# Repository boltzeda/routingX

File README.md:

# routingX

**routingX** is an automated PCB routing tool designed to route already placed KiCad PCB layouts. It takes a placed PCB as input, identifies unrouted connections, and attempts to complete the routing while respecting the board's design constraints.

The router generates a routed KiCad PCB file along with routing reports that help users inspect the routing results and identify any remaining unrouted connections.

## Features

- **Automated PCB Routing:** Routes unrouted connections in an already placed KiCad PCB.
- **Design Rule Awareness:** Supports routing-rule configuration through an optional DRC JSON file.
- **Configurable Via Cost:** Allows users to control the cost associated with via insertion.
- **Partial Routing Support:** Generates a partially routed PCB when all connections cannot be completed.
- **Routing Reports:** Produces JSON reports containing routing results and route details.
- **KiCad Compatibility:** Uses KiCad's PCB tools and Python bindings for board processing.

## Prerequisites

### 1. KiCad 10

Install KiCad 10 with the PCB Editor's `pcbnew` Python binding and `kicad-cli`.

Download KiCad from the [official KiCad download page](https://www.kicad.org/download/).

Linux users can refer to the [distribution-specific installation instructions](https://www.kicad.org/download/linux-distros/).

Verify the installation:

```bash
kicad-cli version
```

Ensure that the `pcbnew` Python module is accessible from the Python environment used to run the router.

### 2. Python

Python **3.13 or later** is required.

Verify your Python version:

```bash
python --version
```

### 3. Python Dependencies

Install the required Python packages from `requirements.txt`.

```bash
python -m pip install -r routingX/requirements.txt
```

## Installation

Clone the repository:

```bash
git clone <repository-url>
```

Navigate to the repository directory:

```bash
cd <repository-name>
```

Install the dependencies:

```bash
python -m pip install -r routingX/requirements.txt
```

Make sure KiCad 10 and its Python bindings are properly configured before running the router.

## Usage

The router accepts an already placed KiCad PCB file (`.kicad_pcb`) as input.

Run the following command from the directory containing the `routingX/` package folder:

```bash
python -m routingX path/to/placed_board.kicad_pcb
```

By default, the router generates the following output:

- **Complete routing:** `<board>_routed.kicad_pcb`
- **Partial routing:** `<board>_partial.kicad_pcb`

The output files are generated in the same directory as the input board.

### Custom Output Path

To specify a custom output location:

```bash
python -m routingX path/to/placed_board.kicad_pcb \
    --out path/to/routed_board.kicad_pcb
```

### Command-Line Options

| Argument | Description | Default |
|---|---|---|
| Input PCB | Path to the placed KiCad PCB file | Required |
| `--out <path>` | Specifies the output PCB file path | Automatically generated |
| `--drc <path.json>` | Provides custom routing-rule values | Built-in defaults |
| `--via-cost <value>` | Controls the cost associated with via insertion | `2.0` |
| `--quiet` | Reduces progress and informational output | Disabled |

### Example with Custom Parameters

```bash
python -m routingX boards/example.kicad_pcb \
    --out output/example_routed.kicad_pcb \
    --via-cost 2.0 \
    --quiet
```

To provide custom routing rules:

```bash
python -m routingX boards/example.kicad_pcb \
    --drc config/drc_rules.json \
    --out output/example_routed.kicad_pcb
```

If no DRC configuration is provided, the router uses its built-in defaults and raises them to satisfy the board's minimum constraints.

## Output Files

The router generates the following files depending on the routing result:

| Output | Description |
|---|---|
| `*_routed.kicad_pcb` | KiCad PCB file generated when routing is complete. |
| `*_partial.kicad_pcb` | Partially routed PCB file generated when some connections remain unrouted. |
| Routing result JSON | Summary of the routing execution and its result. |
| `<output-path>.routes.json` | Detailed routing information for inspection and analysis. |

The partial PCB output allows users to open the board in KiCad and inspect completed and remaining connections.

## Design Rule Verification

After routing, always perform a Design Rule Check (DRC) using KiCad's native DRC functionality.

A successful routing result indicates that the router completed its routing task. However, it does not guarantee that the board is free from all electrical, physical, or manufacturing-related violations.

Recommended verification:

1. Open the generated PCB file in KiCad PCB Editor.
2. Run the native Design Rule Checker (DRC).
3. Inspect unrouted connections, clearance violations, and other reported issues.
4. Review the board before proceeding to manufacturing.

## License

This project is licensed under the **MIT License**.

See the [LICENSE](LICENSE) file for more information.

## Acknowledgements

routingX is part of the BoltzPCB ecosystem, focused on automating and improving PCB design workflows.

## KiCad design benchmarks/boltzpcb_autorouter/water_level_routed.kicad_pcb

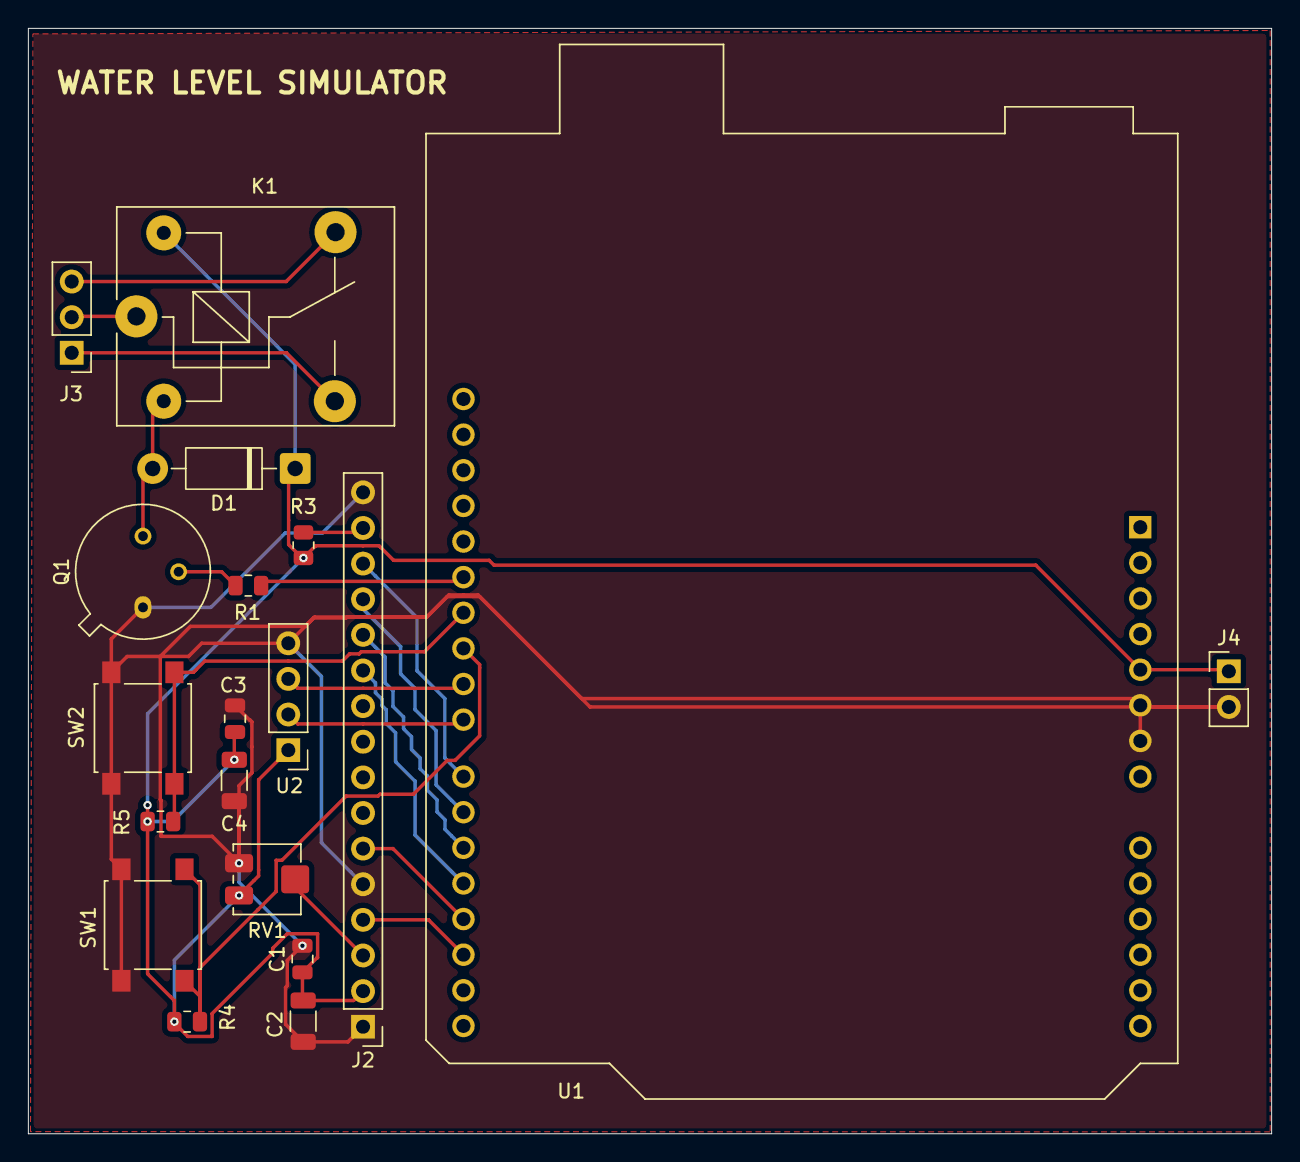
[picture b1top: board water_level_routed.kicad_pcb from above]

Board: 2 copper layers, 88.6 x 78.8 mm, 19 parts (0 on the bottom side), 20 nets.

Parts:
C1, C3: 100nF; C_0805_2012Metric
C2, C4: 10uF; C_1206_3216Metric
D1: 1N4007; D_DO-41_SOD81_P10.16mm_Horizontal
J2: Conn_01x16_Pin; PinHeader_1x16_P2.54mm_Vertical
J3: RELAY_OUT; PinHeader_1x03_P2.54mm_Vertical
J4: POWER_IN; PinHeader_1x02_P2.54mm_Vertical
K1: SANYOU_SRD_Form_C; Relay_SPDT_SANYOU_SRD_Series_Form_C
Q1: 2N2219; TO-39-3
R1: 1k; R_0805_2012Metric
R3: 220R; R_0805_2012Metric
R4, R5: 10k; R_0805_2012Metric
RV1: 10k; Potentiometer_Bourns_3224J_Horizontal
SW1: SET; SW_SPST_B3S-1000
SW2: AUTO/MANUAL; SW_SPST_B3S-1000
U1: Arduino_UNO_R3
U2: HC-SR04; PinHeader_1x04_P2.54mm_Vertical

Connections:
+5V: C1.1, C2.1, C3.1, C4.1, D1.1 (K), J2.2, J4.1, K1.5, R3.2, R4.1, R5.1, RV1.1, U1.5 (+5V), U2.1
/A: J2.15, R3.1
/AUTO_MODE: R5.2, SW2.1, U1.26 (D11)
/BTN_SET: R4.2, SW1.1, U1.25 (D10)
/COM: J3.2, K1.1
/ECHO: U1.24 (D9), U2.3
/LCD_D4: J2.11, U1.19 (D4)
/LCD_D5: J2.12, U1.20 (D5)
/LCD_D6: J2.13, U1.21 (D6)
/LCD_D7: J2.14, U1.22 (D7)
/LCD_E: J2.6, U1.18 (D3)
/LCD_RS: J2.4, U1.17 (D2)
/NC: J3.3, K1.4
/NO: J3.1, K1.3
/RELAY_CTRL: R1.1, U1.27 (D12)
/TRIG: U1.23 (D8), U2.2
/VO: J2.3, RV1.2
GND: C1.2, C2.2, C3.2, C4.2, J2.1, J2.5, J2.16, J4.2, Q1.1 (E), RV1.3, SW1.2, SW2.2, U1.6 (GND), U1.7 (GND), U2.4
unnamed: D1.2 (A), K1.2, Q1.3 (C)
unnamed: Q1.2 (B), R1.2

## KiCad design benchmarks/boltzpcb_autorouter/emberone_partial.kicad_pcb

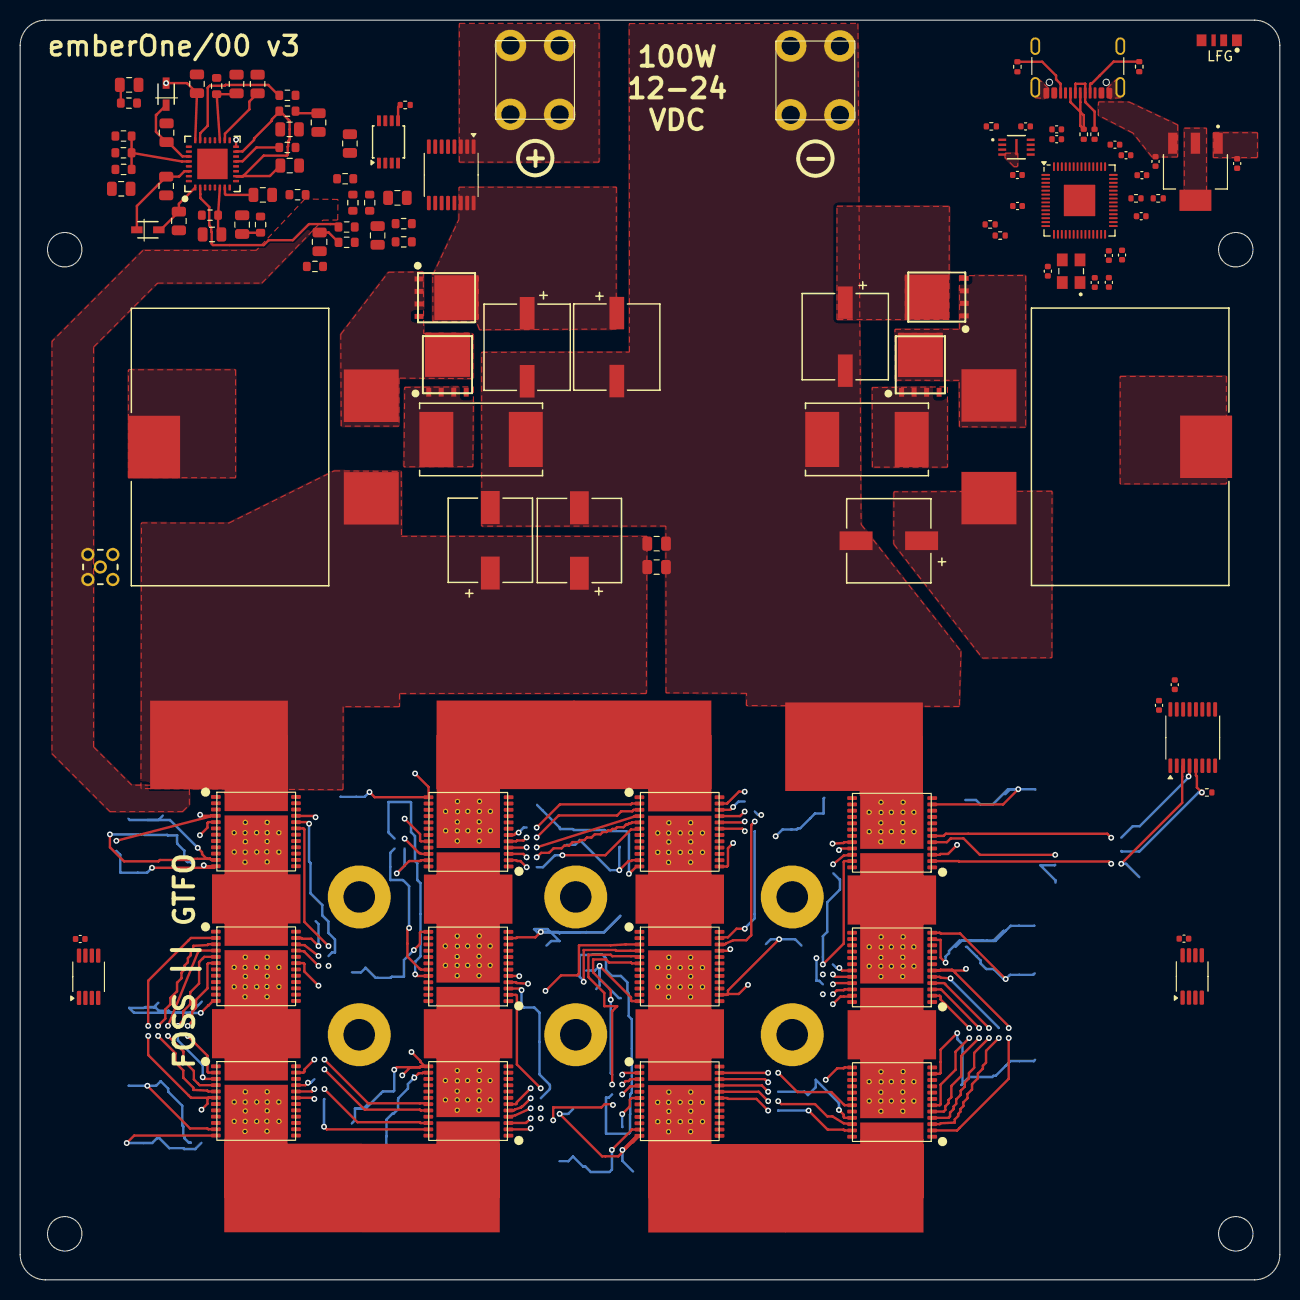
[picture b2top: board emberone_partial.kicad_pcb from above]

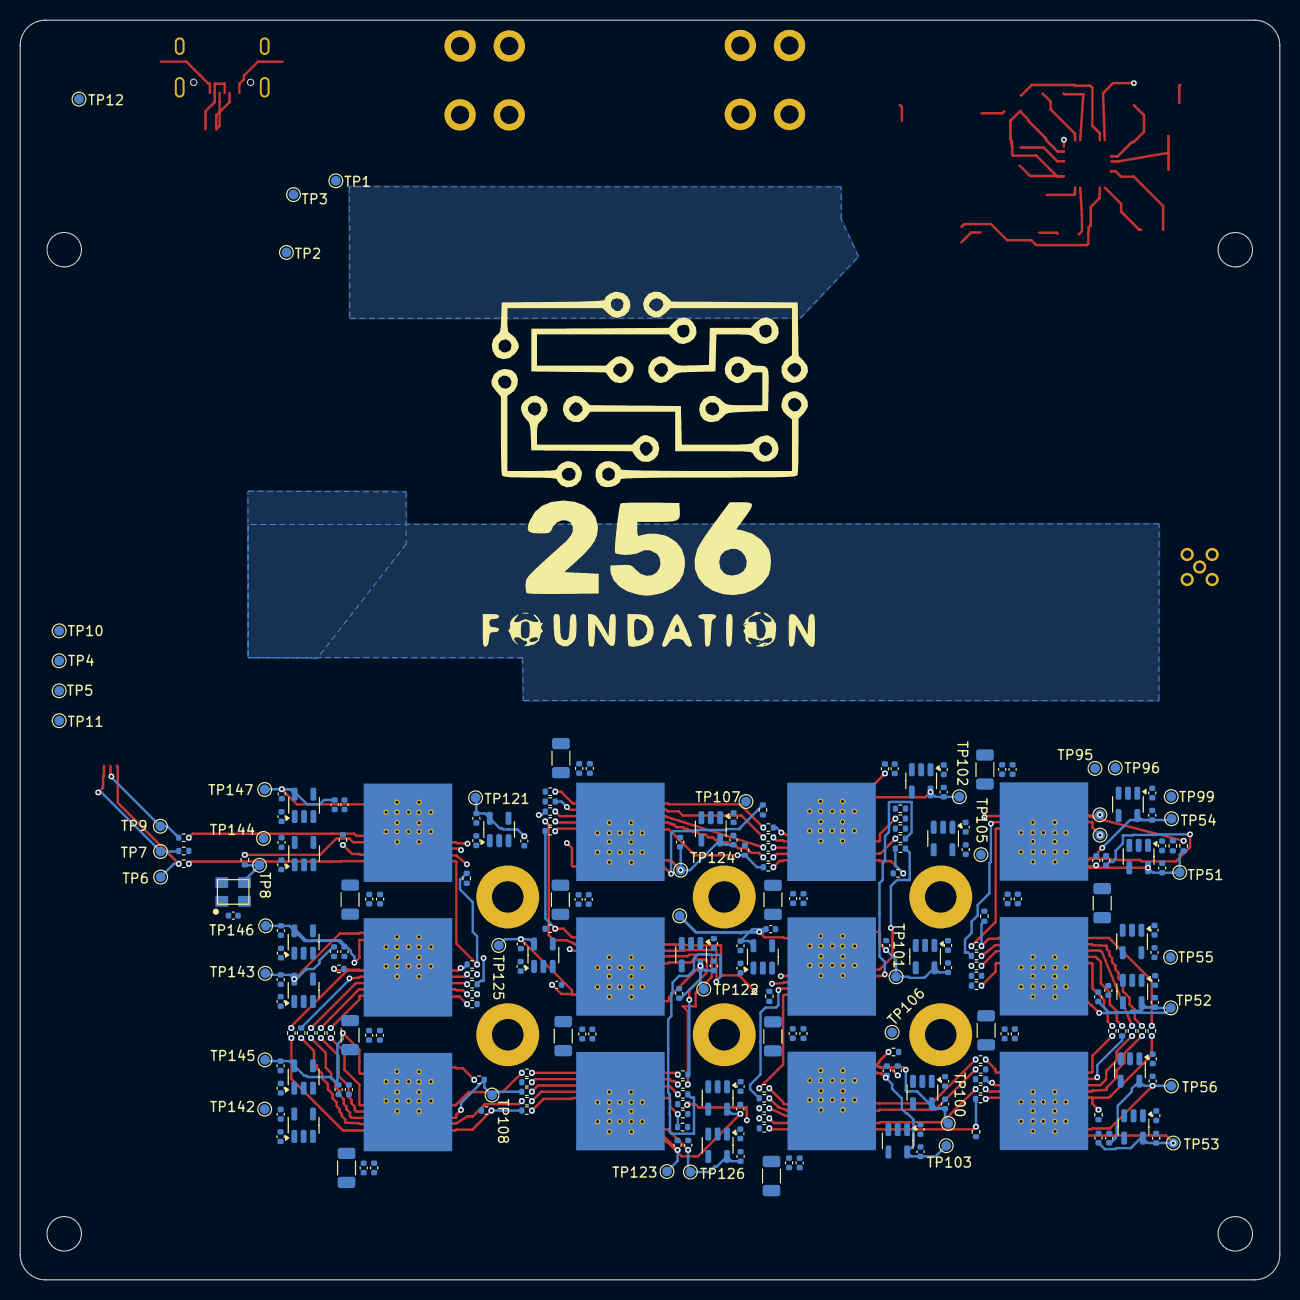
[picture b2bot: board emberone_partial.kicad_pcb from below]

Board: 6 copper layers, 128.0 x 128.0 mm, 395 parts (255 on the bottom side), 225 nets.

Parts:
C1, C3, C4: 82uF; PCAP_SVP_E12_PAN
C2, C27: 0.1uF; C_0805_2012Metric
C5, C14, C19, C20, C26: 1uF; C_0805_2012Metric
C6, C10: 820pF; C_0805_2012Metric
C7, C9, C11: 0.015uF; C_0805_2012Metric
C8: 0.47uF; C_0805_2012Metric
C12: 330pF; C_0805_2012Metric
C13, C15: 0.22uF; C_0805_2012Metric
C16, C17, C18: 470uF; CHEMI-H80
C21, C22, C23, C24, C25, C99, C100, C101, C104, C105, C106, C107, C108, C109, C110, C168, C169, C170, C201, C202, C203, C234, C235, C236, C267, C268, C269: 0.1uF; C_0402_1005Metric
C28, C29: 4700pF; C_0805_2012Metric
C30, C31: 1000pF; C_0805_2012Metric
C90, C98, C102, C103, C111, C112, C113, C115, C116, C117, C118, C119, C120, C122, C156, C157, C159, C160, C161, C162, C163, C164, C174, C175, C176, C180, C181, C182, C183, C184, C185, C186, C187, C188, C189, C190, C191, C192, C193, C194, C195, C196, C197, C207, C208, C209, C213, C214, C215, C216, C217, C218, C219, C220, C221, C222, C223, C224, C225, C226, C227, C228, C229, C230, C240, C241, C242, C246, C247, C248, C249, C250, C251, C252, C253, C254, C255, C256, C257, C258, C259, C260, C261, C262, C263, C273, C274, C275: 1uF; C_0402_1005Metric
C96, C97: 30pF; C_0402_1005Metric
C177, C178, C179, C210, C211, C212, C243, C244, C245, C276, C277, C278: 100uF; C_1206_3216Metric
D1, D2: XBS104S13R-G; SDO_4S13R-G_TOR
EXTRA1: 70x90mm Heatsink; 70x90mm_heatsink
H1, H2, H3, H4: MountingHole; MountingHole_3.5mm
H5, H6, H7, H8, H9, H10: MountingHole; MountingHole_3.2mm_M3_Pad
J1, J2: Screw Terminal; 7770-screw-terminal
J3, J4, J5, J7, J8, J9, J10, J11: Conn_01x01; 5x9_powertab
J6: USB_C_Receptacle_USB2.0; USB_C_Receptacle_GCT_USB4105-xx-A_16P_TopMnt_Horizontal
J12, J14, J16, J18, J21: Conn_01x01; 14x9_powertab_L
J13, J15, J17: Conn_01x01; 14x9_powertab_R
J19: Conn_Coaxial; SAMTEC_MMCX-P-P-H-ST-TH1
L1, L2: 3.3uH; IND_SER2915L_COC
LOGO1: 256 Foundation Logo; 256foundation_logo
Q1, Q2, Q3, Q4: CSD18511Q5A; DQJ0008A
R1: 56.2k; R_0603_1608Metric
R2: 9.09k; R_0603_1608Metric
R3: 44.2k; R_0603_1608Metric
R4: 11k; R_0603_1608Metric
R5, R9: 86.6k; R_0603_1608Metric
R6: 3.57k; R_0603_1608Metric
R7: 1.02k; R_0603_1608Metric
R8, R10: 3m; WSR-4527
R11: 39k; R_0402_1005Metric
R12, R13, R14, R15, R16, R53, R54, R57, R58, R59, R60, R62, R63, R65, R75, R79, R83, R88, R89, R90, R91, R92, R93, R94, R95, R96, R97, R98, R99, R100, R101, R102, R106, R107, R108, R109, R110, R111, R112, R113, R114, R115, R116, R117, R118, R119, R120, R124, R125, R126, R127, R128, R129, R130, R131, R132, R133, R135, R136, R137, R138: 33; R_0402_1005Metric
R17, R56, R85, R86, R87, R103, R104, R105, R121, R122, R123, R134: 2k; R_0402_1005Metric
R18, R50: 10k; R_0402_1005Metric
R19, R20: 4.7k; R_0402_1005Metric
R21, R22: 100k; R_0402_1005Metric
R23, R26, R29, R30, R31, R32: 10; R_0603_1608Metric
R24, R25, R33: 0; R_0603_1608Metric
R27, R28: 6.8; R_0603_1608Metric
R51, R52: 5.1k; R_0402_1005Metric
R64, R66, R67, R68, R69: 1k; R_0402_1005Metric
TP1, TP2, TP3, TP4, TP5, TP6, TP7, TP8, TP9, TP10, TP11, TP12, TP51, TP52, TP53, TP54, TP55, TP56, TP95, TP96, TP97, TP98, TP99, TP100, TP101, TP102, TP103, TP104, TP105, TP106, TP107, TP108, TP121, TP122, TP123, TP124, TP125, TP126, TP142, TP143, TP144, TP145, TP146, TP147: TestPoint; TestPoint_Pad_D1.0mm
U1: LM25119PSQ/NOPB; SQA32A
U2: DS4432U+; TSSOP-8_3x3mm_P0.65mm
U3: INA260; TSSOP-16_4.4x5mm_P0.65mm
U4: SN74AVC4T774; TSSOP-16_4.4x5mm_P0.65mm
U5: 25MHz; SMD3225-4P
U6, U7: TMP1075; HVSSOP-8_3x3mm_P0.65mm
U8: W25Q16JVUXIQ TR; USON-8_UX_2x3x0p6_WIN
U9: SK6812; LED-SMD_4P-L4.0-W1.6-L
U10: TLV1117LV33DCYR; VREG_TLV1117LV33DCYR
U27: RP2040; QFN-56-1EP_7x7mm_P0.4mm_EP3.2x3.2mm
U28, U29, U30, U48, U49, U50, U57, U58, U59, U66, U67, U68: MCP1824T-1202E/OT; SOT-23-5
U32, U42, U43, U51, U52, U53, U60, U61, U62, U69, U70, U71: MCP1824T-0802E; SOT-23-5
U45, U47, U54, U56, U63, U65, U72, U74: BM1362AC_MODE1; BM1362AC
U46, U55, U64, U73: BM1362AC_MODE0; BM1362AC
Y1: 12MHz; XTAL_ECS-120-20-33-CKM-TR3

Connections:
/3V3: C19.1, C20.1, C22.1, C24.1, C25.1, C98.1, C99.2, C103.2, C104.2, C105.2, C106.2, C107.2, C108.2, C109.2, C110.2, R19.1, R20.2, R50.1, U2.8 (VCC), U3.10 (VS), U4.15 (VCCB), U6.6 (A1), U6.8 (V+), U7.6 (A1), U7.7 (A0), U7.8 (V+), U8.8 (VCC), U10.2 (VOUT), U10.4 (VOUT), U27.1 (IOVDD), U27.10 (IOVDD), U27.22 (IOVDD), U27.26 (RUN), U27.33 (IOVDD), U27.42 (IOVDD), U27.43 (ADC_AVDD), U27.44 (VREG_IN), U27.48 (USB_VDD), U27.49 (IOVDD)
/3V6: C16.1, C17.1, C18.1, C26.1, C27.1, C168.1, C174.1, C177.1, J18.1, J19.1 (In), L1.1, L2.2, R6.1, R21.1, U45.25 (VDD)
/5V: C90.1, C111.1, C112.1, C113.1, C118.1, C119.1, C120.1, C180.1, C181.1, C182.1, C186.1, C187.1, C188.1, C213.1, C214.1, C215.1, C219.1, C220.1, C221.1, C246.1, C247.1, C248.1, C252.1, C253.1, C254.1, J6.A4B9 (VBUS), J6.B4A9 (VBUS), U9.2 (VDD), U10.3 (VIN), U28.1 (VIN), U28.3 (EN), U29.1 (VIN), U29.3 (EN), U30.1 (VIN), U30.3 (EN), U32.1 (VIN), U32.3 (EN), U42.1 (VIN), U42.3 (EN), U43.1 (VIN), U43.3 (EN), U48.1 (VIN), U48.3 (EN), U49.1 (VIN), U49.3 (EN), U50.1 (VIN), U50.3 (EN), U51.1 (VIN), U51.3 (EN), U52.1 (VIN), U52.3 (EN), U53.1 (VIN), U53.3 (EN), U57.1 (VIN), U57.3 (EN), U58.1 (VIN), U58.3 (EN), U59.1 (VIN), U59.3 (EN), U60.1 (VIN), U60.3 (EN), U61.1 (VIN), U61.3 (EN), U62.1 (VIN), U62.3 (EN), U66.1 (VIN), U66.3 (EN), U67.1 (VIN), U67.3 (EN), U68.1 (VIN), U68.3 (EN), U69.1 (VIN), U69.3 (EN), U70.1 (VIN), U70.3 (EN), U71.1 (VIN), U71.3 (EN)
/Data/1V1: C100.2, C101.2, C102.2, U27.23 (DVDD), U27.45 (VREG_VOUT), U27.50 (DVDD)
/Data/PWR_EN: R33.1, U27.2 (GPIO0)
/Data/QSPI_SCLK: U8.6 (CLK), U27.52 (QSPI_SCLK)
/Data/QSPI_SD0: U8.5 (DI(IO0)), U27.53 (QSPI_SD0)
/Data/QSPI_SD1: U8.2 (DO(IO1)), U27.55 (QSPI_SD1)
/Data/QSPI_SD2: U8.3 (/WP(IO2)), U27.54 (QSPI_SD2)
/Data/QSPI_SD3: U8.7 (/HOLDOR/RESET(IO3)), U27.51 (QSPI_SD3)
/Data/QSPI_SS: R50.2, U8.1 (/CS), U27.56 (QSPI_SS)
/Data/SCL: R20.1, TP1.1, U2.2 (SCL), U3.9 (SCL), U6.2 (SCL), U7.2 (SCL), U27.18 (GPIO15)
/Data/SDA: R19.2, TP2.1, U2.1 (SDA), U3.8 (SDA), U6.1 (SDA), U7.1 (SDA), U27.17 (GPIO14)
/Data/SWCLK: J6.A8 (SBU1), U27.24 (SWCLK)
/Data/SWD: J6.B8 (SBU2), U27.25 (SWD)
/Data/USB_DN: J6.A7 (D-), J6.B7 (D-), R54.1
/Data/USB_DP: J6.A6 (D+), J6.B6 (D+), R53.1
/Data/XIN: C97.2, U27.20 (XIN), Y1.3
/Data/XOUT: C96.2, U27.21 (XOUT), Y1.1
/Power/LOOP1: Q2.1 (S), Q2.2 (S), Q2.3 (S), R8.1, R31.2
/Power/LOOP2: Q4.1 (S), Q4.2 (S), Q4.3 (S), R10.1, R29.2
/Power/OUT0: C11.1, C12.1, R6.2, R7.1, U1.9 (FB1), U2.6 (OUT0)
/Power/SW1: C13.2, C28.1, L1.2, Q1.1 (S), Q1.2 (S), Q1.3 (S), Q2.5 (D), Q2.6 (D), Q2.7 (D), Q2.8 (D), R5.2, U1.32 (SW1)
/Power/SW2: C15.2, C29.1, L2.1, Q3.1 (S), Q3.2 (S), Q3.3 (S), Q4.5 (D), Q4.6 (D), Q4.7 (D), Q4.8 (D), R9.2, U1.25 (SW2)
/Power/VIN: J1.1, U3.1 (IN+), U3.2 (IN+), U3.3 (IN+), U3.12 (VBUS)
/Power/VIN_M: C1.1, C2.1, C3.1, C4.1, Q1.5 (D), Q1.6 (D), Q1.7 (D), Q1.8 (D), Q3.5 (D), Q3.6 (D), Q3.7 (D), Q3.8 (D), R1.1, U1.29 (VIN), U3.14 (IN-), U3.15 (IN-), U3.16 (IN-)
/RST: TP10.1, U4.14 (B1), U27.14 (GPIO11)
/RX: TP5.1, U4.12 (B3), U27.12 (GPIO9)
/TX: TP4.1, U4.13 (B2), U27.11 (GPIO8)
/stack4/0V8-0: C122.1, C159.1, TP54.1, U32.5 (VOUT), U45.11 (VDDIO_08_0)
/stack4/0V8-1: C156.1, C160.1, TP55.1, U42.5 (VOUT), U46.11 (VDDIO_08_0)
/stack4/0V8-2: C157.1, C161.1, TP56.1, U43.5 (VOUT), U47.11 (VDDIO_08_0)
/stack4/1V2-0: C115.1, C162.1, R64.1, TP51.1, U28.5 (VOUT), U45.12 (VDDIO_18_0)
/stack4/1V2-1: C116.1, C163.1, TP52.1, U29.5 (VOUT), U46.12 (VDDIO_18_0)
/stack4/1V2-2: C117.1, C164.1, TP53.1, U30.5 (VOUT), U47.12 (VDDIO_18_0)
/stack4/BI: R100.2, U47.20 (BI)
/stack4/CI: R94.2, U47.23 (CI)
/stack4/CLKI: R96.2, U47.22 (CLKI)
/stack4/GND0: C111.2, C115.2, C118.2, C122.2, C159.2, C162.2, C168.2, C169.1, C174.2, C175.1, C177.2, C178.1, J3.1, R86.2, U28.2 (GND), U32.2 (GND), U45.1 (VSS), U45.10 (VSS), U45.15 (PLL_VSS), U45.17 (PIN_MODE), U45.18 (VSS), U45.24 (VSS), U45.26 (VSS), U46.25 (VDD)
/stack4/GND1: C112.2, C116.2, C119.2, C156.2, C160.2, C163.2, C169.2, C170.1, C175.2, C176.1, C178.2, C179.1, J4.1, R85.2, U29.2 (GND), U42.2 (GND), U46.1 (VSS), U46.10 (VSS), U46.15 (PLL_VSS), U46.18 (VSS), U46.24 (VSS), U46.26 (VSS), U47.25 (VDD)
/stack4/GND2: C113.2, C117.2, C120.2, C157.2, C161.2, C164.2, C170.2, C176.2, C179.2, C201.1, C207.1, C210.1, J12.1, J13.1, R56.2, U30.2 (GND), U43.2 (GND), U47.1 (VSS), U47.10 (VSS), U47.15 (PLL_VSS), U47.17 (PIN_MODE), U47.18 (VSS), U47.24 (VSS), U47.26 (VSS), U54.25 (VDD)
/stack4/NRSTI: R102.2, U47.19 (NRSTI)
/stack4/RO: R98.2, U47.21 (RO)
/stack5/0V8-0: C189.1, C192.1, TP103.1, U51.5 (VOUT), U54.14 (VDDIO_08_1)
/stack5/0V8-1: C190.1, C193.1, TP104.1, U52.5 (VOUT), U55.11 (VDDIO_08_0)
/stack5/0V8-2: C191.1, C194.1, TP105.1, U53.5 (VOUT), U56.14 (VDDIO_08_1)
/stack5/1V2-0: C183.1, C195.1, R66.1, TP100.1, U48.5 (VOUT), U54.13 (VDDIO_18_1)
/stack5/1V2-1: C184.1, C196.1, TP101.1, U49.5 (VOUT), U55.13 (VDDIO_18_1)
/stack5/1V2-2: C185.1, C197.1, TP102.1, U50.5 (VOUT), U56.13 (VDDIO_18_1)
/stack5/BI: R114.2, U56.3 (BI)
/stack5/CI: R120.2, U56.6 (CI)
/stack5/CLKI: R118.2, U56.5 (CLKI)
/stack5/GND0: C180.2, C183.2, C186.2, C189.2, C192.2, C195.2, C201.2, C202.1, C207.2, C208.1, C210.2, C211.1, J5.1, R104.2, U48.2 (GND), U51.2 (GND), U54.1 (VSS), U54.10 (VSS), U54.15 (PLL_VSS), U54.18 (VSS), U54.24 (VSS), U54.26 (VSS), U55.25 (VDD)
/stack5/GND1: C181.2, C184.2, C187.2, C190.2, C193.2, C196.2, C202.2, C203.1, C208.2, C209.1, C211.2, C212.1, J7.1, R87.2, U49.2 (GND), U52.2 (GND), U55.1 (VSS), U55.10 (VSS), U55.15 (PLL_VSS), U55.17 (PIN_MODE), U55.18 (VSS), U55.24 (VSS), U55.26 (VSS), U56.25 (VDD)
/stack5/GND2: C182.2, C185.2, C188.2, C191.2, C194.2, C197.2, C203.2, C209.2, C212.2, C234.1, C240.1, C243.1, J14.1, J15.1, R103.2, U50.2 (GND), U53.2 (GND), U56.1 (VSS), U56.10 (VSS), U56.15 (PLL_VSS), U56.18 (VSS), U56.24 (VSS), U56.26 (VSS), U63.25 (VDD)
/stack5/NRSTI: R112.2, U56.2 (NRSTI)
/stack5/RO: R116.2, U56.4 (RO)
/stack6/0V8-0: C222.1, C225.1, TP124.1, U60.5 (VOUT), U63.11 (VDDIO_08_0)
/stack6/0V8-1: C223.1, C226.1, TP125.1, U61.5 (VOUT), U64.14 (VDDIO_08_1)
/stack6/0V8-2: C224.1, C227.1, TP126.1, U62.5 (VOUT), U65.11 (VDDIO_08_0)
/stack6/1V2-0: C216.1, C228.1, TP121.1, U57.5 (VOUT), U63.13 (VDDIO_18_1)
/stack6/1V2-0B: R67.1, U63.12 (VDDIO_18_0)
/stack6/1V2-1: C217.1, C229.1, TP122.1, U58.5 (VOUT), U64.12 (VDDIO_18_0)
/stack6/1V2-2: C218.1, C230.1, TP123.1, U59.5 (VOUT), U65.12 (VDDIO_18_0)
/stack6/BI: R15.2, U65.20 (BI)
/stack6/CI: R12.2, U65.23 (CI)
/stack6/CLKI: R13.2, U65.22 (CLKI)
/stack6/GND0: C213.2, C216.2, C219.2, C222.2, C225.2, C228.2, C234.2, C235.1, C240.2, C241.1, C243.2, C244.1, J8.1, R122.2, U57.2 (GND), U60.2 (GND), U63.1 (VSS), U63.10 (VSS), U63.15 (PLL_VSS), U63.17 (PIN_MODE), U63.18 (VSS), U63.24 (VSS), U63.26 (VSS), U64.25 (VDD)
/stack6/GND1: C214.2, C217.2, C220.2, C223.2, C226.2, C229.2, C235.2, C236.1, C241.2, C242.1, C244.2, C245.1, J9.1, R121.2, U58.2 (GND), U61.2 (GND), U64.1 (VSS), U64.10 (VSS), U64.15 (PLL_VSS), U64.18 (VSS), U64.24 (VSS), U64.26 (VSS), U65.25 (VDD)
/stack6/GND2: C215.2, C218.2, C221.2, C224.2, C227.2, C230.2, C236.2, C242.2, C245.2, C267.1, C273.1, C276.1, J16.1, J17.1, R105.2, U59.2 (GND), U62.2 (GND), U65.1 (VSS), U65.10 (VSS), U65.15 (PLL_VSS), U65.17 (PIN_MODE), U65.18 (VSS), U65.24 (VSS), U65.26 (VSS), U72.25 (VDD)
/stack6/NRSTI: R16.2, U65.19 (NRSTI)
/stack6/RO: R14.2, U65.21 (RO)
/stack7/0V8-0: C255.1, C258.1, TP145.1, U69.5 (VOUT), U72.11 (VDDIO_08_0)
/stack7/0V8-1: C256.1, C259.1, TP146.1, U70.5 (VOUT), U73.11 (VDDIO_08_0)
/stack7/0V8-2: C257.1, C260.1, TP147.1, U71.5 (VOUT), U74.11 (VDDIO_08_0)
/stack7/1V2-0: C249.1, C261.1, TP142.1, U66.5 (VOUT), U72.12 (VDDIO_18_0)
/stack7/1V2-0B: R68.1, U72.13 (VDDIO_18_1)
/stack7/1V2-1: C250.1, C262.1, TP143.1, U67.5 (VOUT), U73.12 (VDDIO_18_0)
/stack7/1V2-2: C21.1, C23.2, C251.1, C263.1, R69.1, TP144.1, U4.7 (DIR3), U4.8 (DIR4), U4.16 (VCCA), U5.1 (EN), U5.4 (VIN), U68.5 (VOUT), U74.12 (VDDIO_18_0)
/stack7/CI: R138.2, TP9.1, U4.4 (A2)
/stack7/CLKI: R137.2, TP8.1, U5.3 (OUT)
/stack7/GND0: C246.2, C249.2, C252.2, C255.2, C258.2, C261.2, C267.2, C268.1, C273.2, C274.1, C276.2, C277.1, J10.1, R17.2, U66.2 (GND), U69.2 (GND), U72.1 (VSS), U72.10 (VSS), U72.15 (PLL_VSS), U72.18 (VSS), U72.24 (VSS), U72.26 (VSS), U73.25 (VDD)
/stack7/GND1: C247.2, C250.2, C253.2, C256.2, C259.2, C262.2, C268.2, C269.1, C274.2, C275.1, C277.2, C278.1, J11.1, R123.2, U67.2 (GND), U70.2 (GND), U73.1 (VSS), U73.10 (VSS), U73.15 (PLL_VSS), U73.17 (PIN_MODE), U73.18 (VSS), U73.24 (VSS), U73.26 (VSS), U74.25 (VDD)
/stack7/RO: R69.2, R136.2, TP7.1, U4.5 (A3)
/stack7/RST_N: R135.2, TP6.1, U4.3 (A1)
GND: C1.2, C2.2, C3.2, C4.2, C5.2, C6.2, C7.2, C8.2, C9.2, C10.2, C14.1, C16.2, C17.2, C18.2, C19.2, C20.2, C21.2, C22.2, C23.1, C24.2, C25.2, C26.2, C27.2, C90.2, C96.1, C97.1, C98.2, C99.1, C100.1, C101.1, C102.1, C103.1, C104.1, C105.1, C106.1, C107.1, C108.1, C109.1, C110.1, C248.2, C251.2, C254.2, C257.2, C260.2, C263.2, C269.2, C275.2, C278.2, J2.1, J6.A1B12 (GND), J6.B1A12 (GND), J6.S1 (SHIELD), J19.2 (Ext), J21.1, R2.2, R3.2, R7.2, R8.2, R10.2, R11.2, R18.2, R22.2, R27.2, R28.2, R30.2, R32.2, R51.1, R52.1, R134.2, TP3.1, TP11.1, U1.3 (PGND1), U1.12 (AGND), U1.22 (PGND2), U1.33 (PAD), U2.4 (GND), U3.4 (A1), U3.5 (A0), U3.6 (GND), U3.11 (GND), U4.1 (DIR1), U4.2 (DIR2), U4.6 (A4), U4.9 (OE), U4.10 (GND), U5.2 (GND), U6.4 (GND), U6.5 (A2), U6.7 (A0), U7.4 (GND), U7.5 (A2), U8.4 (GND), U8.9 (EPAD), U9.4 (GND), U10.1 (GND), U27.19 (TESTEN), U27.57 (GND), U68.2 (GND), U71.2 (GND), U74.1 (VSS), U74.10 (VSS), U74.15 (PLL_VSS), U74.18 (VSS), U74.24 (VSS), U74.26 (VSS), Y1.2, Y1.4
unnamed: C11.2, R4.1
unnamed: C28.2, R27.1
unnamed: C29.2, R28.1
unnamed: C5.1, D1.2 (A), U1.1 (VCC1), U1.17 (DEMB)
unnamed: C13.1, D1.1 (K), U1.30 (HB1)
unnamed: C14.2, D2.2 (A), U1.16 (FB2), U1.24 (VCC2)
unnamed: C15.1, D2.1 (K), U1.27 (HB2)
unnamed: J6.A5 (CC1), R51.2
unnamed: J6.B5 (CC2), R52.2
unnamed: Q1.4 (G), R23.2
unnamed: Q2.4 (G), R24.2
unnamed: Q3.4 (G), R26.2
unnamed: Q4.4 (G), R25.2
unnamed: C12.2, R4.2, U1.10 (COMP1), U1.15 (COMP2)
unnamed: C31.2, R31.1, U1.5 (CS1)
unnamed: C30.2, R29.1, U1.20 (CS2)
unnamed: C31.1, R32.1, U1.4 (CSG1)
unnamed: C30.1, R30.1, U1.21 (CSG2)
unnamed: R23.1, U1.31 (HO1)
unnamed: R26.1, U1.26 (HO2)
unnamed: R24.1, U1.2 (LO1)
unnamed: R25.1, U1.23 (LO2)
unnamed: C10.1, R5.1, U1.6 (RAMP1)
unnamed: C6.1, R9.1, U1.19 (RAMP2)
unnamed: C8.1, U1.14 (RES)
unnamed: R3.1, U1.13 (RT)
unnamed: C9.1, U1.7 (SS1)
unnamed: C7.1, U1.18 (SS2)
unnamed: R1.2, R2.1, R33.2, U1.28 (UVLO)
unnamed: R11.1, U2.5 (FS0)
unnamed: TP12.1, U9.1 (DIN), U27.3 (GPIO1)
unnamed: R21.2, R22.1, U27.38 (GPIO26_ADC0)
unnamed: R54.2, U27.46 (USB_DM)
unnamed: R53.2, U27.47 (USB_DP)
unnamed: R65.1, U45.20 (BI)
unnamed: TP98.1, U45.5 (BO)
unnamed: R83.1, U45.23 (CI)
unnamed: R79.1, U45.22 (CLKI)
unnamed: TP96.1, U45.3 (CLKO)
unnamed: TP95.1, U45.2 (CO)
unnamed: R63.1, U45.19 (NRSTI)
unnamed: R86.1, TP99.1, U45.6 (NRSTO)
unnamed: R64.2, TP97.1, U45.4 (RI)
unnamed: R75.1, U45.21 (RO)
unnamed: R58.1, U46.3 (BI)
unnamed: R65.2, U46.22 (BO)
unnamed: R62.1, U46.6 (CI)
unnamed: R60.1, U46.5 (CLKI)
unnamed: R79.2, U46.20 (CLKO)
unnamed: R83.2, U46.19 (CO)
unnamed: R57.1, U46.2 (NRSTI)
unnamed: R63.2, R85.1, U46.23 (NRSTO)
unnamed: R75.2, U46.21 (RI)
unnamed: R59.1, U46.4 (RO)
unnamed: R58.2, U47.5 (BO)
unnamed: R60.2, U47.3 (CLKO)
unnamed: R62.2, U47.2 (CO)
unnamed: R56.1, R57.2, U47.6 (NRSTO)
unnamed: R59.2, U47.4 (RI)
unnamed: R89.1, U54.3 (BI)
unnamed: R100.1, U54.22 (BO)
unnamed: R92.1, U54.6 (CI)
unnamed: R91.1, U54.5 (CLKI)
unnamed: R96.1, U54.20 (CLKO)
unnamed: R94.1, U54.19 (CO)
unnamed: R88.1, U54.2 (NRSTI)
unnamed: R102.1, R104.1, U54.23 (NRSTO)
unnamed: R66.2, R98.1, TP106.1, U54.21 (RI)
unnamed: R90.1, U54.4 (RO)
unnamed: R95.1, U55.20 (BI)
unnamed: R89.2, U55.5 (BO)
unnamed: R101.1, U55.23 (CI)
unnamed: R99.1, U55.22 (CLKI)
unnamed: R91.2, U55.3 (CLKO)
unnamed: R92.2, U55.2 (CO)
unnamed: R93.1, U55.19 (NRSTI)
unnamed: R87.1, R88.2, U55.6 (NRSTO)
unnamed: R90.2, U55.4 (RI)
unnamed: R97.1, U55.21 (RO)
unnamed: R95.2, U56.22 (BO)
unnamed: R99.2, U56.20 (CLKO)
unnamed: R101.2, U56.19 (CO)
unnamed: R93.2, R103.1, U56.23 (NRSTO)
unnamed: R97.2, U56.21 (RI)
unnamed: R113.1, U63.20 (BI)
unnamed: R114.1, U63.5 (BO)
unnamed: R119.1, U63.23 (CI)
unnamed: R117.1, U63.22 (CLKI)
unnamed: R118.1, U63.3 (CLKO)
unnamed: R120.1, U63.2 (CO)
unnamed: R111.1, U63.19 (NRSTI)
unnamed: R112.1, R122.1, U63.6 (NRSTO)
unnamed: R67.2, R116.1, TP107.1, U63.4 (RI)
unnamed: R115.1, U63.21 (RO)
unnamed: R107.1, U64.3 (BI)
unnamed: R113.2, U64.22 (BO)
unnamed: R110.1, U64.6 (CI)
unnamed: R109.1, U64.5 (CLKI)
unnamed: R117.2, U64.20 (CLKO)
unnamed: R119.2, U64.19 (CO)
unnamed: R106.1, U64.2 (NRSTI)
unnamed: R111.2, R121.1, U64.23 (NRSTO)
unnamed: R115.2, U64.21 (RI)
unnamed: R108.1, U64.4 (RO)
unnamed: R107.2, U65.5 (BO)
unnamed: R109.2, U65.3 (CLKO)
unnamed: R110.2, U65.2 (CO)
unnamed: R105.1, R106.2, U65.6 (NRSTO)
unnamed: R108.2, U65.4 (RI)
unnamed: R125.1, U72.3 (BI)
unnamed: R15.1, U72.22 (BO)
unnamed: R128.1, U72.6 (CI)
unnamed: R127.1, U72.5 (CLKI)
unnamed: R13.1, U72.20 (CLKO)
unnamed: R12.1, U72.19 (CO)
unnamed: R124.1, U72.2 (NRSTI)
unnamed: R16.1, R17.1, U72.23 (NRSTO)
unnamed: R14.1, R68.2, TP108.1, U72.21 (RI)
unnamed: R126.1, U72.4 (RO)
unnamed: R130.1, U73.20 (BI)
unnamed: R125.2, U73.5 (BO)
unnamed: R133.1, U73.23 (CI)
unnamed: R132.1, U73.22 (CLKI)
unnamed: R127.2, U73.3 (CLKO)
unnamed: R128.2, U73.2 (CO)
unnamed: R129.1, U73.19 (NRSTI)
unnamed: R123.1, R124.2, U73.6 (NRSTO)
unnamed: R126.2, U73.4 (RI)
unnamed: R131.1, U73.21 (RO)
unnamed: R18.1, U74.3 (BI)
unnamed: R130.2, U74.22 (BO)
unnamed: R138.1, U74.6 (CI)
unnamed: R137.1, U74.5 (CLKI)
unnamed: R132.2, U74.20 (CLKO)
unnamed: R133.2, U74.19 (CO)
unnamed: R135.1, U74.2 (NRSTI)
unnamed: R129.2, R134.1, U74.23 (NRSTO)
unnamed: R131.2, U74.21 (RI)
unnamed: R136.1, U74.4 (RO)

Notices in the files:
benchmarks/boltzpcb_autorouter/seven_partial.kicad_pcb:
Licensed under CERN-OHL-P v2
parts and their libraries:
License: Apache-2.0
COPYRIGHT: Copyright 2012-2025 Great Scott Gadgets
LICENSE: Licensed under the CERN-OHL-P v2
